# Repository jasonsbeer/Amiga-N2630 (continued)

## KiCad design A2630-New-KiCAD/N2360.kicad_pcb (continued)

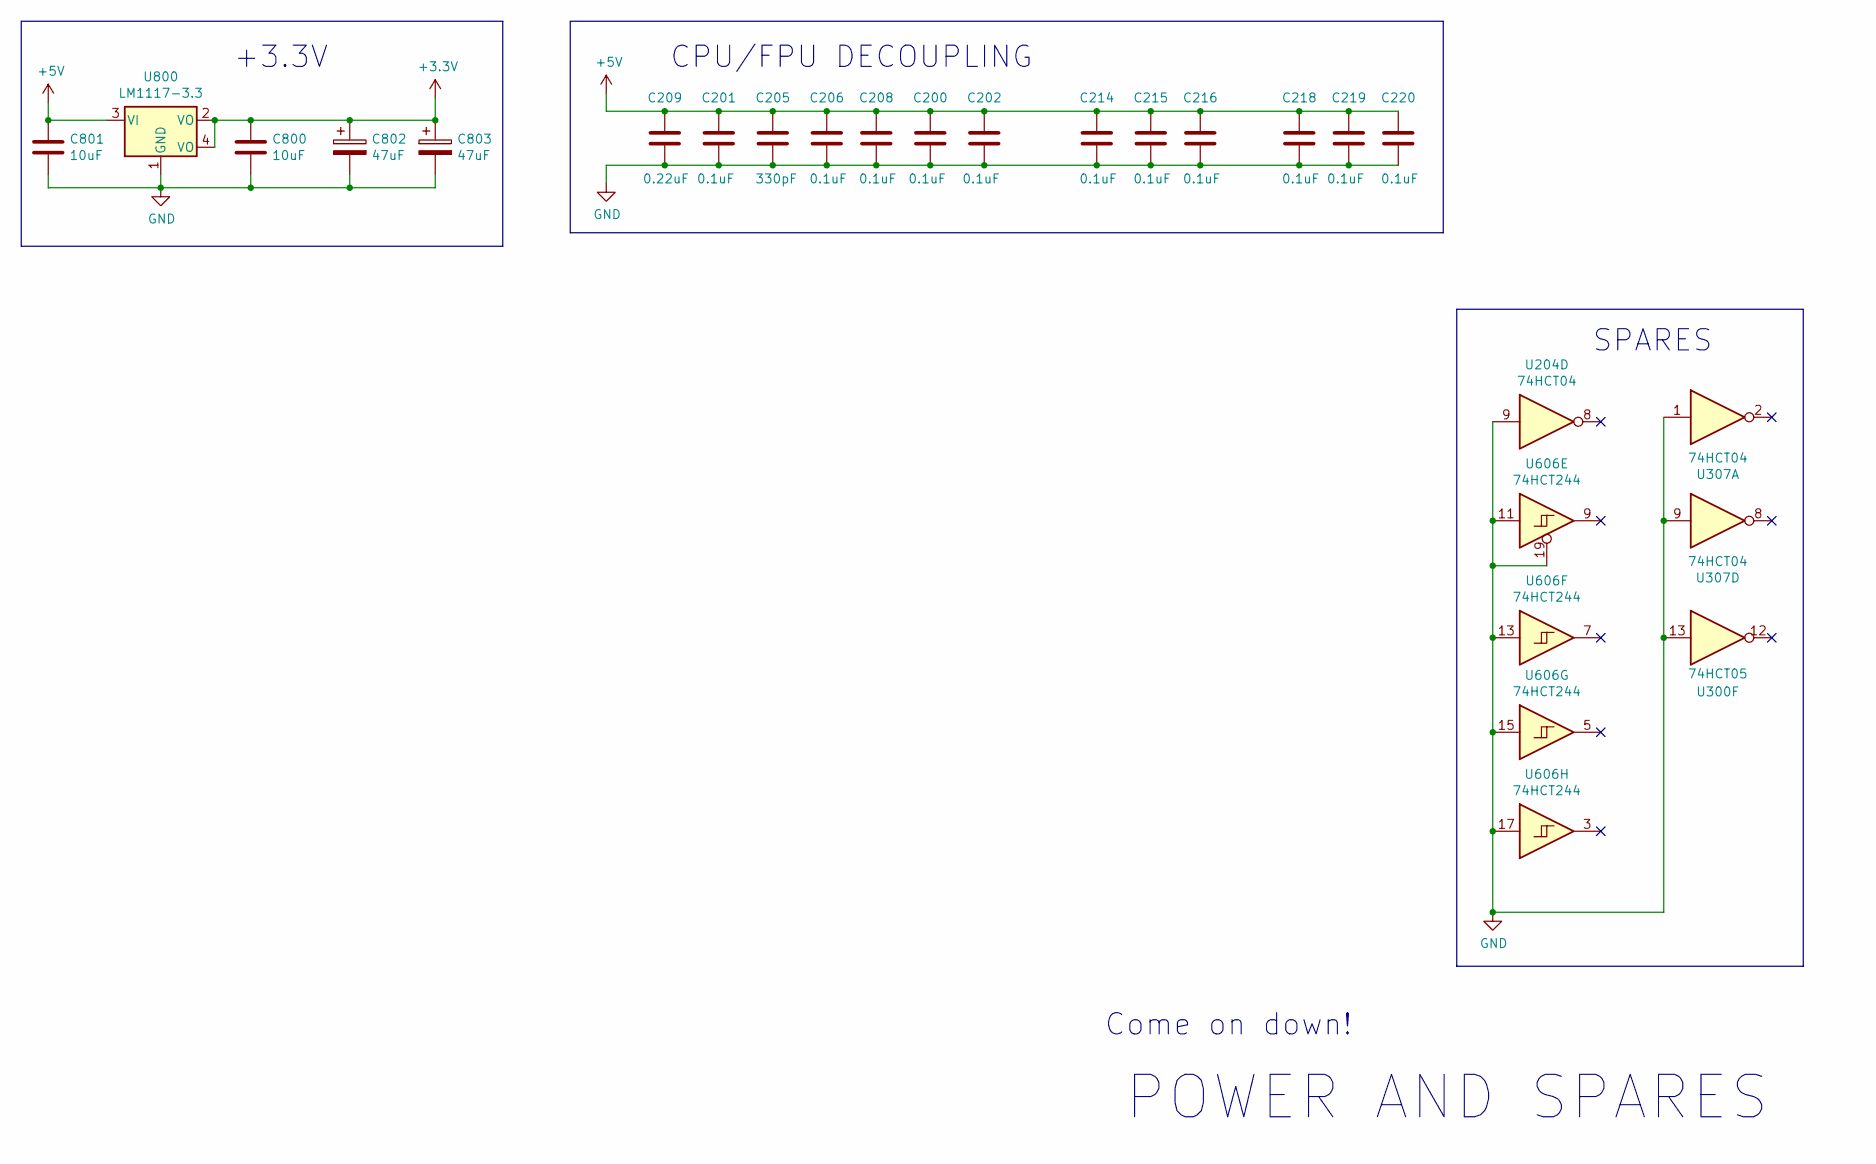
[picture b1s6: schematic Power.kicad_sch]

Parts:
C200, C201, C202, C206, C208, C214, C215, C216, C218, C219, C220: 0.1uF; C_0805_2012Metric
C205: 330pF; C_0805_2012Metric
C209: 0.22uF; C_0805_2012Metric
C800, C801: 10uF; R_0805_2012Metric
C802, C803: 47uF; CP_Radial_D5.0mm_P2.00mm
U204: 74HCT04; SOIC-14_3.9x8.7mm_P1.27mm; Digikey 296-31832-1-ND
U300: 74HCT05; SOIC-14_3.9x8.7mm_P1.27mm
U307: 74HCT04; SOIC-14_3.9x8.7mm_P1.27mm
U606: 74HCT244; SOIC-20W_7.5x12.8mm_P1.27mm
U800: LM1117-3.3; SOT-223

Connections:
+3V3: C800.1, C802.1, C803.1, U800.2 (VO), U800.4 (VO); also elsewhere on the board

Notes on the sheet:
POWER AND SPARES
Come on down!
SPARES
+3.3V
CPU/FPU DECOUPLING

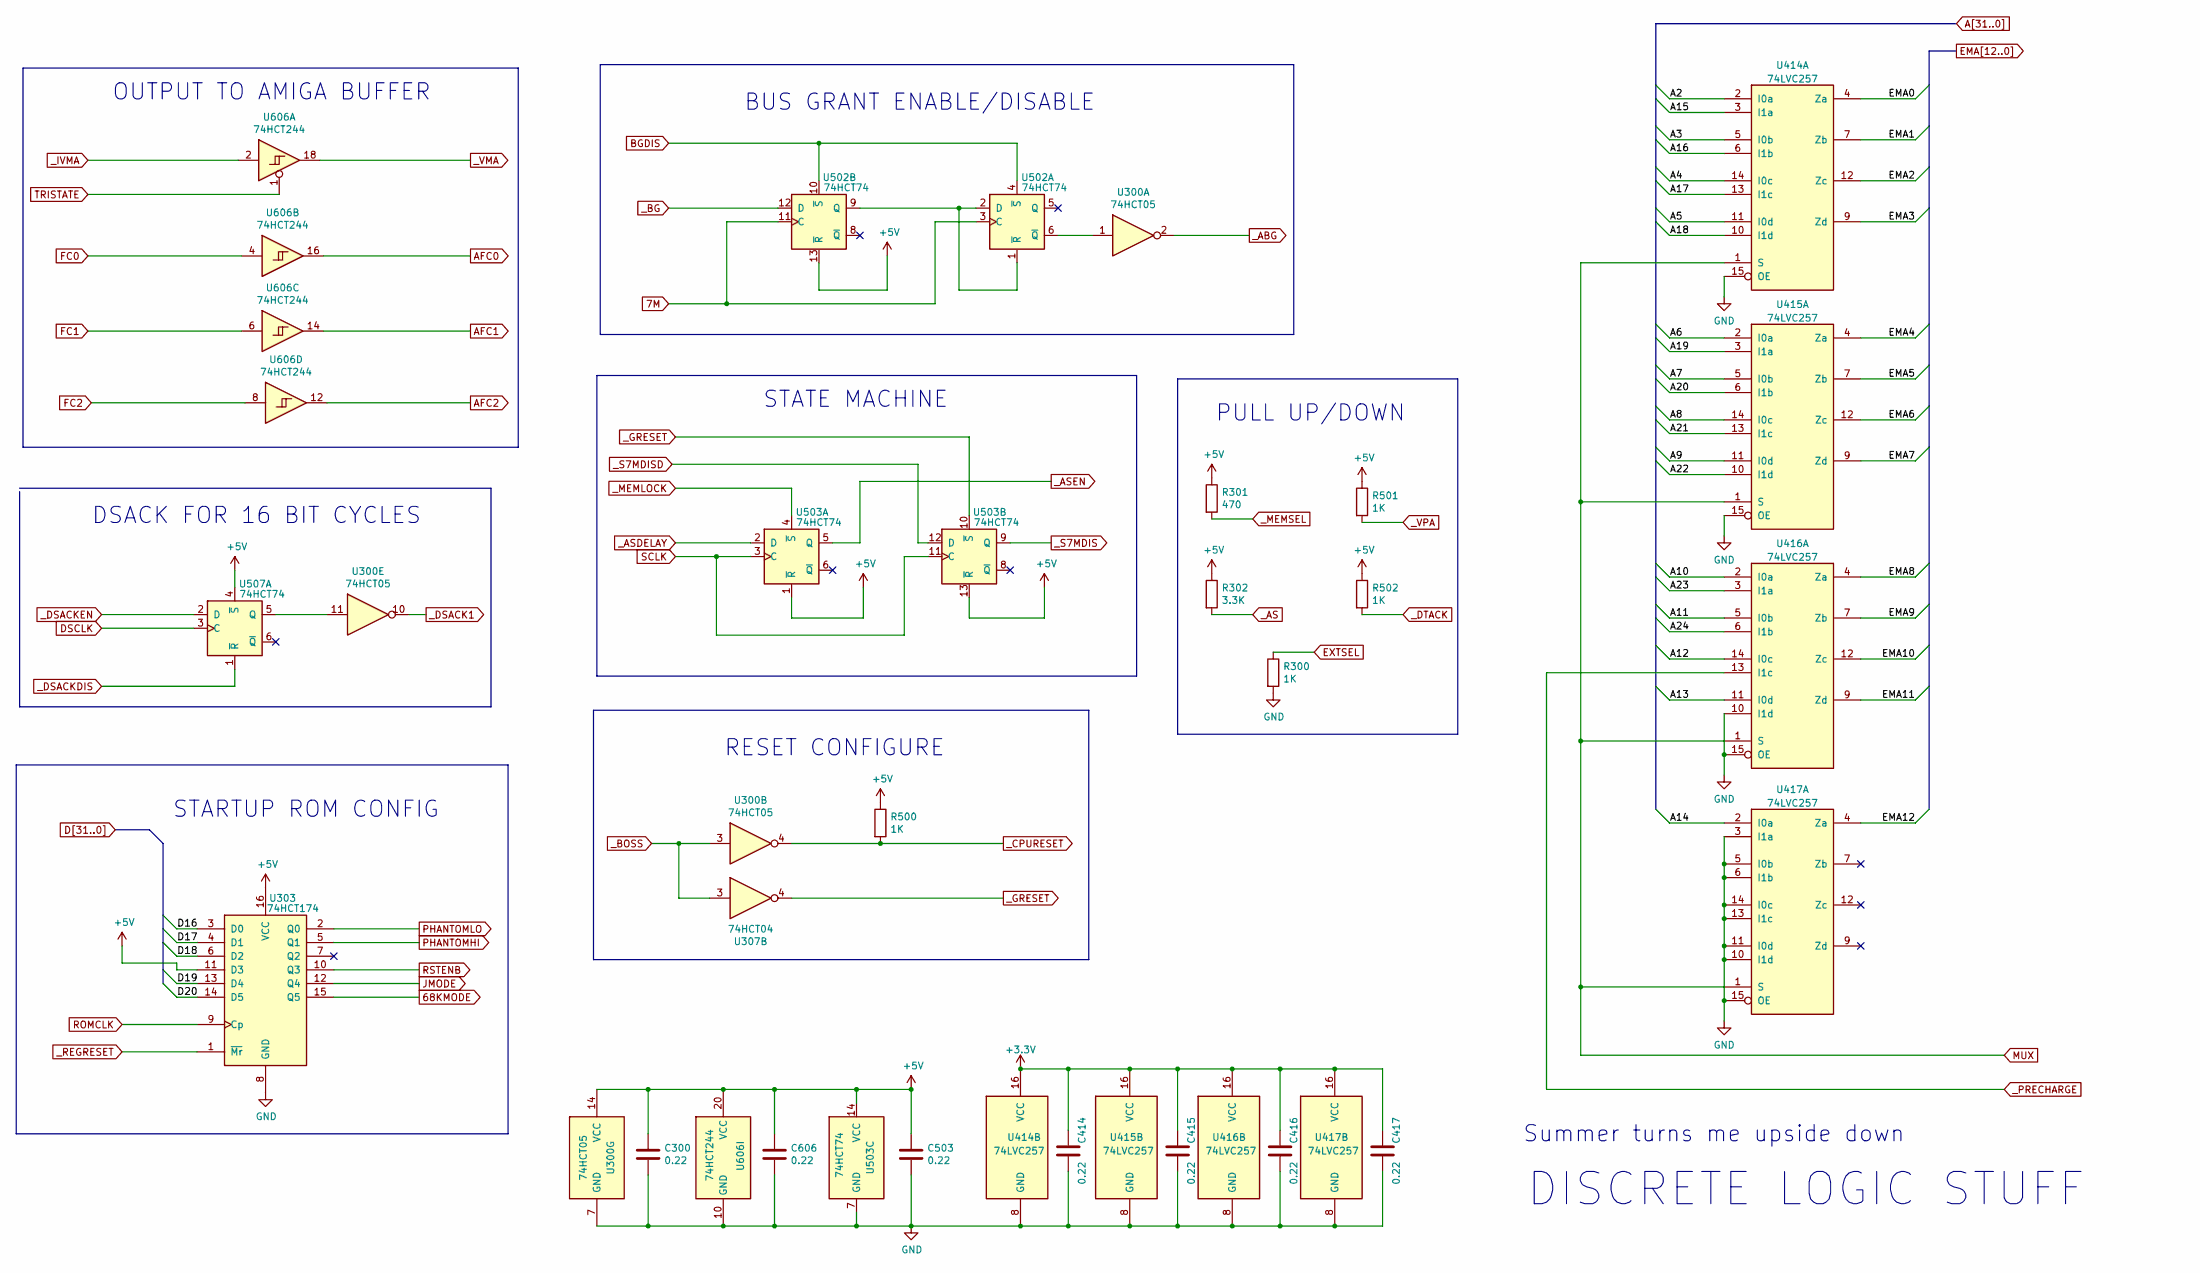
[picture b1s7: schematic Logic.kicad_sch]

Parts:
C300, C414, C415, C416, C417, C503, C606: 0.22; C_0805_2012Metric
R300, R500, R501, R502: 1K; R_0805_2012Metric
R301: 470; R_0805_2012Metric
R302: 3.3K; R_0805_2012Metric
U300: 74HCT05; SOIC-14_3.9x8.7mm_P1.27mm
U303: 74HCT174; SOIC-16_3.9x9.9mm_P1.27mm
U307: 74HCT04; SOIC-14_3.9x8.7mm_P1.27mm
U414, U415, U416, U417: 74LVC257; SOIC-16_3.9x9.9mm_P1.27mm
U502, U503, U507: 74HCT74; SOIC-14_3.9x8.7mm_P1.27mm
U606: 74HCT244; SOIC-20W_7.5x12.8mm_P1.27mm

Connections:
7M: U502.3 (C), U502.11 (C); also elsewhere on the board
68KMODE: U303.15 (Q5)
+3V3: C414.1, C415.1, C416.1, C417.1, U414.16 (VCC), U415.16 (VCC), U416.16 (VCC), U417.16 (VCC); also elsewhere on the board
A2: U414.2 (I0a); also elsewhere on the board
A3: U414.5 (I0b); also elsewhere on the board
A4: U414.14 (I0c); also elsewhere on the board
A5: U414.11 (I0d); also elsewhere on the board
A6: U415.2 (I0a); also elsewhere on the board
A7: U415.5 (I0b); also elsewhere on the board
A8: U415.14 (I0c); also elsewhere on the board
A9: U415.11 (I0d); also elsewhere on the board
A10: U416.2 (I0a); also elsewhere on the board
A11: U416.5 (I0b); also elsewhere on the board
A12: U416.14 (I0c); also elsewhere on the board
A13: U416.11 (I0d); also elsewhere on the board
A14: U417.2 (I0a); also elsewhere on the board
A15: U414.3 (I1a); also elsewhere on the board
A16: U414.6 (I1b); also elsewhere on the board
A17: U414.13 (I1c); also elsewhere on the board
A18: U414.10 (I1d); also elsewhere on the board
A19: U415.3 (I1a); also elsewhere on the board
A20: U415.6 (I1b); also elsewhere on the board
A21: U415.13 (I1c); also elsewhere on the board
A22: U415.10 (I1d); also elsewhere on the board
A23: U416.3 (I1a); also elsewhere on the board
A24: U416.6 (I1b); also elsewhere on the board
AFC0: U606.16; also elsewhere on the board
AFC1: U606.14; also elsewhere on the board
AFC2: U606.12; also elsewhere on the board
BGDIS: U502.4 (~S), U502.10 (~S)
D16: U303.3 (D0); also elsewhere on the board
D17: U303.4 (D1); also elsewhere on the board
D18: U303.6 (D2); also elsewhere on the board
D19: U303.13 (D4); also elsewhere on the board
D20: U303.14 (D5); also elsewhere on the board
DSCLK: U507.3 (C); also elsewhere on the board
EMA0: U414.4 (Za); also elsewhere on the board
EMA1: U414.7 (Zb); also elsewhere on the board
EMA2: U414.12 (Zc); also elsewhere on the board
EMA3: U414.9 (Zd); also elsewhere on the board
EMA4: U415.4 (Za); also elsewhere on the board
EMA5: U415.7 (Zb); also elsewhere on the board
EMA6: U415.12 (Zc); also elsewhere on the board
EMA7: U415.9 (Zd); also elsewhere on the board
EMA8: U416.4 (Za); also elsewhere on the board
EMA9: U416.7 (Zb); also elsewhere on the board
EMA10: U416.12 (Zc); also elsewhere on the board
EMA11: U416.9 (Zd); also elsewhere on the board
EMA12: U417.4 (Za); also elsewhere on the board
EXTSEL: R300.1; also elsewhere on the board
FC0: U606.4; also elsewhere on the board
FC1: U606.6; also elsewhere on the board
FC2: U606.8; also elsewhere on the board
JMODE: U303.12 (Q4); also elsewhere on the board
MUX: U414.1 (S), U415.1 (S), U416.1 (S), U417.1 (S); also elsewhere on the board
unnamed: U300.1, U502.6 (~Q)
unnamed: U300.11, U507.5 (Q)
unnamed: U502.1 (~R), U502.2 (D), U502.9 (Q)
PHANTOMHI: U303.5 (Q1); also elsewhere on the board
PHANTOMLO: U303.2 (Q0); also elsewhere on the board
ROMCLK: U303.9 (Cp); also elsewhere on the board
RSTENB: U303.10 (Q3)
SCLK: U503.3 (C), U503.11 (C); also elsewhere on the board
TRISTATE: U606.1; also elsewhere on the board
_ABG: U300.2; also elsewhere on the board
_AS: R302.2; also elsewhere on the board
_ASDELAY: U503.2 (D); also elsewhere on the board
_ASEN: U503.5 (Q); also elsewhere on the board
_BG: U502.12 (D); also elsewhere on the board
_BOSS: U300.3, U307.3; also elsewhere on the board
_CPURESET: R500.2, U300.4; also elsewhere on the board
_DSACK1: U300.10; also elsewhere on the board
_DSACKDIS: U507.1 (~R); also elsewhere on the board
_DSACKEN: U507.2 (D); also elsewhere on the board
_DTACK: R502.2; also elsewhere on the board
_GRESET: U307.4, U503.10 (~S); also elsewhere on the board
_IVMA: U606.2; also elsewhere on the board
_MEMLOCK: U503.4 (~S); also elsewhere on the board
_MEMSEL: R301.2; also elsewhere on the board
_PRECHARGE: U416.13 (I1c); also elsewhere on the board
_REGRESET: U303.1 (~Mr); also elsewhere on the board
_S7MDIS: U503.9 (Q); also elsewhere on the board
_S7MDISD: U503.12 (D); also elsewhere on the board
_VMA: U606.18; also elsewhere on the board
_VPA: R501.2; also elsewhere on the board

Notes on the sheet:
STARTUP ROM CONFIG
PULL UP/DOWN
RESET CONFIGURE
Summer turns me upside down
DSACK FOR 16 BIT CYCLES
DISCRETE LOGIC STUFF
OUTPUT TO AMIGA BUFFER
BUS GRANT ENABLE/DISABLE
STATE MACHINE

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
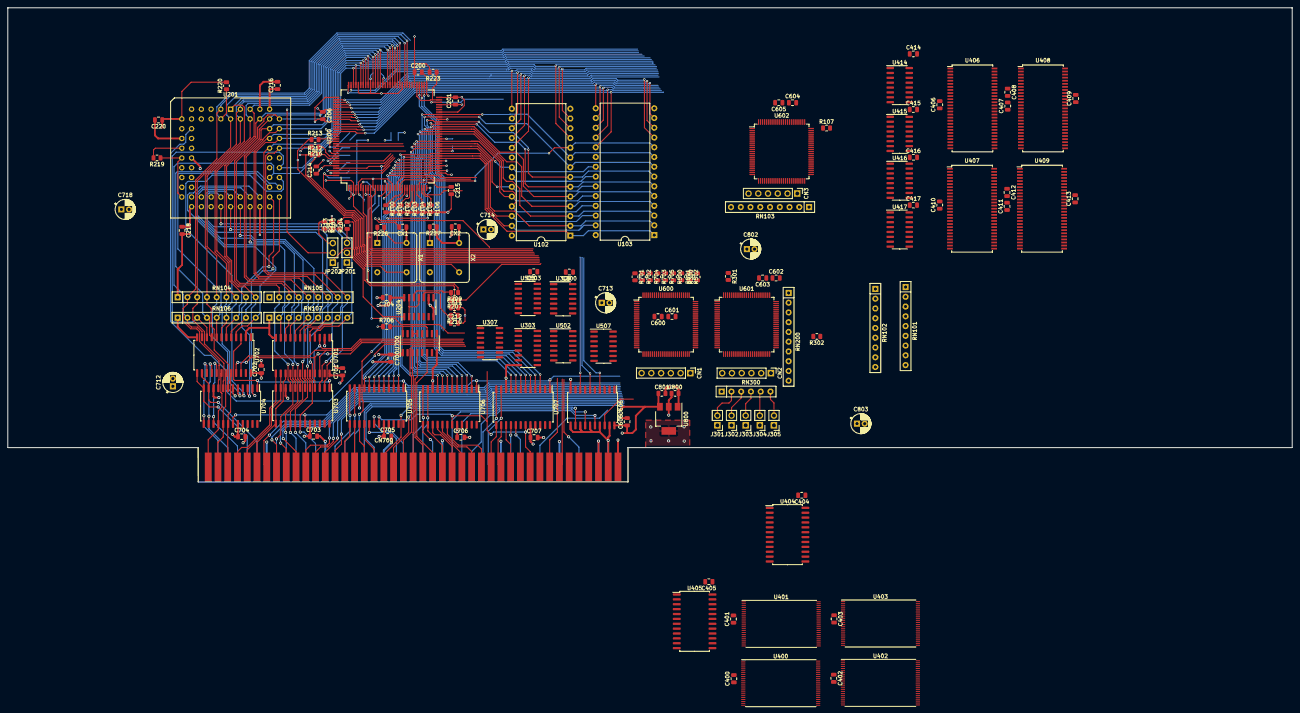
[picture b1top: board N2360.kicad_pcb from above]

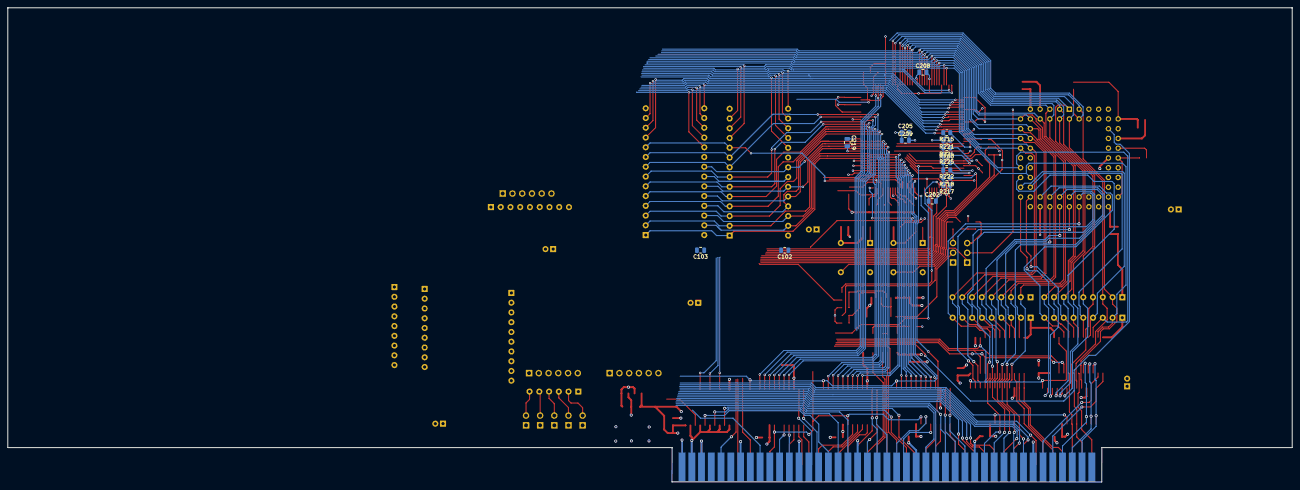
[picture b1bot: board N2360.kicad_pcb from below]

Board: 4 copper layers, 334.4 x 123.5 mm, 166 parts (15 on the bottom side), 297 nets.

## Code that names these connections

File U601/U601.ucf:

NET "nBGACK"		LOC = "P1" ;
NET "EXTSEL"		LOC = "P3" ;
NET "PHANTOMLO"	LOC = "P4" ;
NET "PHANTOMHI"	LOC = "P6" ;
NET "FC<0>"			LOC = "P8" ;
NET "FC<1>"			LOC = "P9" ;
NET "nSENSE"		LOC = "P12" ; 
NET "nBERR"			LOC = "P13" ;
NET "nCPURESET"	LOC = "P14" ;
NET "CPUCLK"		LOC = "P22" ; //15
NET "nMEMLOCK"		LOC = "P16" ;
NET "nASEN"			LOC = "P17" ;
NET "nEXTERN"		LOC = "P18" ;
//NET "nMEMSEL"		LOC = "P20" ;
NET "nONBOARD"		LOC = "P15" ; //22
NET "nDSEN"			LOC = "P23" ;
NET "nCYCEND"		LOC = "P25" ;
NET "CONFIGED"		LOC = "P27" ;
//NET "ARnW"			LOC = "P28" ;
NET "TRISTATE"		LOC = "P29" ;
NET "nUDS"			LOC = "P30" ;
NET "nLDS"			LOC = "P33" ;
NET "MEMACCESS"	LOC = "P39" ; //
NET "nRESET"		LOC = "P37" ; //
//NET "TWOMB"			LOC = "P35" ; //35
NET "Z2AUTO"		LOC = "P36" ; 

//NET "MODE68K"		LOC = "P40" ; //
NET "OSMODE"		LOC = "P42" ; //
//NET "nOE0"			LOC = "P49" ; //
NET "nLMBE"			LOC = "P50" ; //
NET "nLLBE"			LOC = "P52" ; //
NET "nUUBE"			LOC = "P53" ; //
NET "nUMBE"			LOC = "P54" ; //
//NET "nWE0"			LOC = "P55" ; //
NET "SIZ<0>"		LOC = "P56" ; //
NET "SIZ<1>"		LOC = "P58" ; //
//NET "EMDDIR"		LOC = "P59" ; //

NET "A<0>"			LOC = "P60" ; //60
NET "A<1>"			LOC = "P61" ; //61
NET "A<2>"			LOC = "P63" ; //
NET "A<3>"			LOC = "P64" ; //
NET "A<4>"			LOC = "P65" ; //
NET "A<5>"			LOC = "P66" ; //
NET "A<6>"			LOC = "P67" ; //
NET "A<13>"			LOC = "P68" ; //
NET "A<14>"			LOC = "P70" ; //
NET "A<15>"			LOC = "P71" ; //
NET "A<16>"			LOC = "P72" ; //
NET "A<17>"			LOC = "P74" ; //
NET "A<18>"			LOC = "P76" ; //
NET "A<19>"			LOC = "P77" ; //
NET "A<20>"			LOC = "P78" ; //
NET "A<21>"			LOC = "P79" ; //
NET "A<22>"			LOC = "P81" ; //81
NET "A<23>"			LOC = "P82" ; //82

NET "D<28>"			LOC = "P86" ; //86
NET "D<29>"			LOC = "P85" ; 
NET "D<30>"			LOC = "P91" ; //90
NET "D<31>"			LOC = "P89" ; 

NET "nCIIN"			LOC = "P87" ;
NET "FC<2>"			LOC = "P90" ; //91
NET "nAVEC"			LOC = "P92" ;
NET "nDS"			LOC = "P93" ;
NET "nAS"			LOC = "P94" ;
NET "RnW"			LOC = "P95" ;
NET "nFPUCS"		LOC = "P96" ;
NET "nCSROM"		LOC = "P97" ;
NET "ROMCLK"		LOC = "P99" ;

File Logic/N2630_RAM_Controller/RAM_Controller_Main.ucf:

NET	"A<0>"	LOC = "P82"	;
NET	"A<1>"	LOC = "P81"	;
NET	"A<2>"	LOC = "P79"	;
NET	"A<3>"	LOC = "P78"	;
NET	"A<4>"	LOC = "P77"	;
NET	"A<5>"	LOC = "P76"	;
NET	"A<6>"	LOC = "P74"	;
NET	"A<7>"	LOC = "P72"	;
NET	"A<8>"	LOC = "P71"	;
NET	"A<9>"	LOC = "P70"	;
NET	"A<10>"	LOC = "P68"	;
NET	"A<11>"	LOC = "P67"	;
NET	"A<12>"	LOC = "P66"	;
NET	"A<13>"	LOC = "P65"	;
NET	"A<14>"	LOC = "P64"	;
NET	"A<15>"	LOC = "P63"	;
NET	"A<16>"	LOC = "P61"	;
NET	"A<17>"	LOC = "P60"	;
NET	"A<18>"	LOC = "P59"	;
NET	"A<19>"	LOC = "P58"	;
NET	"A<20>"	LOC = "P56"	;
NET	"A<21>"	LOC = "P55"	;
NET	"A<22>"	LOC = "P54"	;
NET	"A<23>"	LOC = "P53"	;
NET	"A<24>"	LOC = "P52"	;
NET	"A<25>"	LOC = "P50"	;
NET	"A<26>"	LOC = "P49"	;
NET	"A<27>"	LOC = "P42"	;
NET	"A<28>"	LOC = "P41"	;
NET	"A<29>"	LOC = "P37"	;
NET	"A<30>"	LOC = "P35"	;
NET	"A<31>"	LOC = "P32"	;

NET	"MA<0>"	LOC = "P13"	;
NET	"MA<1>"	LOC = "P14"	;
NET	"MA<2>"	LOC = "P15"	;
NET	"MA<3>"	LOC = "P16"	;
NET	"MA<4>"	LOC = "P17"	;
NET	"MA<5>"	LOC = "P18"	;
NET	"MA<6>"	LOC = "P20"	;
NET	"MA<7>"	LOC = "P23"	;
NET	"MA<8>"	LOC = "P25"	;
NET	"MA<9>"	LOC = "P27"	;
NET	"MA<10>"	LOC = "P28"	;
NET	"MA<11>"	LOC = "P29"	;
NET	"MA<12>"	LOC = "P30"	;

NET	"D<0>"	LOC = "P3";
NET	"D<1>"	LOC = "P4";
NET	"D<2>"	LOC = "P6";
NET	"D<3>"	LOC = "P8";

NET	"_RAS"	LOC = "P33"	;
NET	"_CAS"	LOC = "P36"	;

NET	"_CBREQ"	LOC = "P87"	;
NET	"_AS"		LOC = "P91"	;
NET	"_DS"		LOC = "P90"	;
NET	"SIZ0"	LOC = "P92"	;
NET	"SIZ1"	LOC = "P93"	;
NET	"_STERM"	LOC = "P94"	;
NET	"_CBACK"	LOC = "P95"	;
NET	"_DSACK0"	LOC = "P96"	;
NET	"_DSACK1"	LOC = "P97"	;

NET	"CPUCLK_A"	LOC = "P22"	;
NET	"_GRESET"	LOC = "P99" ;

NET	"DQM0"	LOC = "P9"	;
NET	"DQM1"	LOC = "P10"	;
NET	"DQM2"	LOC = "P11"	;
NET	"DQM3"	LOC = "P12"	;

NET	"BANK0"	LOC = "P39"	;
NET	"BANK1"	LOC = "P40"	;

NET 	"FC0"		LOC = "P85"	;
NET 	"FC1"		LOC = "P86"	;
NET 	"FC2"		LOC = "P89"	;

#Address Timings
#From the 68030 user manual...
#The processor places the address on the bus at the beginning of 
#a bus cycle. The address is valid while AS is asserted.
#AS is a timing signal that indicates the validity of an address on the address
#bus and of many control signals. It is asserted one-half clock after the 
#beginning of a bus cycle.
INST	"A<0>"	TNM = ADDRESS	;
INST	"A<1>"	TNM = ADDRESS	;
INST	"A<2>"	TNM = ADDRESS	;
INST	"A<3>"	TNM = ADDRESS	;
INST	"A<4>"	TNM = ADDRESS	;
INST	"A<5>"	TNM = ADDRESS	;
INST	"A<6>"	TNM = ADDRESS	;
INST	"A<7>"	TNM = ADDRESS	;
INST	"A<8>"	TNM = ADDRESS	;
INST	"A<9>"	TNM = ADDRESS	;
INST	"A<10>"	TNM = ADDRESS	;
INST	"A<11>"	TNM = ADDRESS	;
INST	"A<12>"	TNM = ADDRESS	;
INST	"A<13>"	TNM = ADDRESS	;
INST	"A<14>"	TNM = ADDRESS	;
INST	"A<15>"	TNM = ADDRESS	;
INST	"A<16>"	TNM = ADDRESS	;
INST	"A<17>"	TNM = ADDRESS	;
INST	"A<18>"	TNM = ADDRESS	;
INST	"A<19>"	TNM = ADDRESS	;
INST	"A<20>"	TNM = ADDRESS	;
INST	"A<21>"	TNM = ADDRESS	;
INST	"A<22>"	TNM = ADDRESS	;
INST	"A<23>"	TNM = ADDRESS	;
INST	"A<24>"	TNM = ADDRESS	;
INST	"A<25>"	TNM = ADDRESS	;
INST	"A<26>"	TNM = ADDRESS	;
INST	"A<27>"	TNM = ADDRESS	;
INST	"A<28>"	TNM = ADDRESS	;
INST	"A<29>"	TNM = ADDRESS	;
INST	"A<30>"	TNM = ADDRESS	;
INST	"A<31>"	TNM = ADDRESS	;
TIMEGRP "ADDRESS" OFFSET - IN 1 ns VALID 100 ns BEFORE "_AS" FALLING;

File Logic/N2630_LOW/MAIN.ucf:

NET "nS7MDISD"	LOC = "P1" ;
NET "SCLK"		LOC = "P3" ;
NET "nS7MDIS"	LOC = "P4" ;
NET "nBOSS"		LOC = "P6" ;
NET "nASDELAY"	LOC = "P8" ;
NET "nDSACKDIS"	LOC = "P9" ;
NET "IPLCLK"	LOC = "P10" ;
NET "nDSACKEN"	LOC = "P11" ;	
NET "nDSCLK"	LOC = "P12" ;

NET "ADDIR"		LOC = "P13" ;
NET "DRSEL"		LOC = "P14"	;
NET "nADOEH"	LOC = "P15" ;
NET "P7M"		LOC = "P16" ;
NET "nC1"		LOC = "P17" ;
NET "nC3"		LOC = "P18" ;
NET "nADOEL"	LOC = "P20" ;
NET "nAAS"		LOC = "P22" ;
NET "nUDS"		LOC = "P23" ;
NET "nLDS"		LOC = "P25" ;
NET "nDTACK"	LOC = "P28" ;
NET "nABG"		LOC = "P29" ;
NET "nABGACK"	LOC = "P30" ;
NET "nABR"		LOC = "P33" ;
NET "nRESET"	LOC = "P35" ;
NET "E"			LOC = "P36" ;
NET "nVPA"		LOC = "P37" ;
NET "nOVR"		LOC = "P39" ;
NET "nBGACK"	LOC = "P40" ;
NET "nIVMA"		LOC = "P41" ;
NET "B2000"		LOC = "P42" ;
NET "TRISTATE"	LOC = "P49" ;	
NET "CONFIGED"	LOC = "P50" ;
NET "ARnW"		LOC = "P52" ;
NET "CDAC"		LOC = "P53" ;
NET "A7M"		LOC = "P54" ;
NET "MEMACCESS"	LOC = "P55" ;	
NET "nBGDIS"		LOC = "P58" ;
NET "nCYCEND"	LOC = "P60" ;
NET "DSEN"		LOC = "P61" ;
NET "nONBOARD"	LOC = "P63" ;
NET "nMEMSEL"	LOC = "P64" ;

NET "nEXTERN"	LOC = "P65" ;
NET "nASEN"		LOC = "P66" ;
NET "CPUCLK"	LOC = "P67" ;
NET "nCPURESET"	LOC = "P68" ;
NET "EXTSEL"	LOC = "P70" ;
NET "FC<2>"		LOC = "P71" ;
NET "FC<1>"		LOC = "P72" ;
NET "FC<0>"		LOC = "P74" ;
NET "n7M"		LOC = "P76" ;
NET "nAS"		LOC = "P85" ;
NET "RnW"		LOC = "P86" ;
NET "nSTERM"	LOC = "P87" ;
NET "nHALT"		LOC = "P90" ;
NET "nDSACK1"	LOC = "P92" ;
NET "nDSACK0"	LOC = "P93" ;
NET "RSTENB"	LOC = "P94" ;
NET "JMODE"		LOC = "P95" ;
NET "MODE68K"	LOC = "P96" ;
NET "nREGRESET"	LOC = "P97" ;

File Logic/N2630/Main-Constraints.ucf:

NET	"A<16>"	LOC = "P"	;
NET	"A<17>"	LOC = "P"	;
NET	"A<18>"	LOC = "P"	;
NET	"A<19>"	LOC = "P"	;
NET	"A<20>"	LOC = "P"	;
NET	"A<21>"	LOC = "P"	;
NET	"A<22>"	LOC = "P"	;
NET	"A<23>"	LOC = "P"	;

NET "PHANTOMHI"	LOC = "P" ;
NET "PHANTOMLO"	LOC = "P" ;

NET "_AS"	LOC = "P" ;
NET "R_W"	LOC = "P" ;
NET "_BOSS"	LOC = "P" ;
NET "_ABG"	LOC = "P" ;
NET "_AAS" 	LOC = "P" ;

NET "FC0"	LOC = "P" ;
NET "FC1"	LOC = "P" ;
NET "FC2"	LOC = "P" ;

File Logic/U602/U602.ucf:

NET "A<0>" 		LOC="P41";
NET "A<1>" 		LOC="P43";
NET "A<2>" 		LOC="P44";
NET "A<3>" 		LOC="P45";
NET "A<4>" 		LOC="P46";
NET "A<5>" 		LOC="P48";
NET "A<6>" 		LOC="P49";
NET "A<7>" 		LOC="P50";
NET "A<8>" 		LOC="P51";
NET "A<9>" 		LOC="P52";
NET "A<10>" 	LOC="P53";
NET "A<11>" 	LOC="P54";
NET "A<12>" 	LOC="P56";
NET "A<13>" 	LOC="P57";
NET "A<14>" 	LOC="P58";
NET "A<15>" 	LOC="P59";
NET "A<16>" 	LOC="P60";
NET "A<17>" 	LOC="P61";
NET "A<18>" 	LOC="P64";
NET "A<19>" 	LOC="P66";
NET "A<20>" 	LOC="P68";
NET "A<21>" 	LOC="P69";
NET "A<22>" 	LOC="P70";
NET "A<23>" 	LOC="P71";
NET "A<24>" 	LOC="P40";
NET "A<25>" 	LOC="P39";
NET "A<26>" 	LOC="P35";
NET "A<27>" 	LOC="P34";
NET "A<28>" 	LOC="P33";
NET "A<29>" 	LOC="P31";
NET "A<30>" 	LOC="P38";
NET "A<31>" 	LOC="P27";

NET "D<24>"		LOC="P4";
NET "D<25>"		LOC="P143";
NET "D<26>"		LOC="P142";
NET "D<27>"		LOC="P22";
NET "D<28>"		LOC="P23";
NET "D<29>"		LOC="P24";
NET "D<30>"		LOC="P25";
NET "D<31>"		LOC="P26";

//NET "nBERR"		LOC="P5";
//NET "nCBREQ"	LOC="P7";
//NET "nCBACK"	LOC="P9";
NET "EXTSEL"	LOC="P10";
NET "nBGACK"	LOC="P11";
NET "nSTERM"	LOC="P12";
NET "FC<0>"		LOC="P13";
NET "FC<1>"		LOC="P14";
NET "FC<2>"		LOC="P15";
//NET "nDSACK0"	LOC="P16";
NET "nDSACK1"	LOC="P17";
NET "nDS"		LOC="P19";
NET "nAS"		LOC="P20";
NET "RnW"		LOC="P21";
NET "CPUCLK"	LOC="P30";
NET "nEM1LLBE"	LOC="P74";
NET "nEM1UMBE"	LOC="P75";
NET "nEM1LMBE"	LOC="P76";
NET "nEM1UUBE"	LOC="P77";
NET "nEM1WE"	LOC="P78";
NET "nCAS1"		LOC="P79";
NET "EM1CLKE"	LOC="P80";
NET "nRAS1"		LOC="P81";
NET "EMA<7>"	LOC="P82";
NET "nEM1CS"	LOC="P83";
NET "EMA<5>"	LOC="P85";
NET "BANK0"		LOC="P86";
NET "EMA<6>"	LOC="P87";
NET "BANK1"		LOC="P88";
NET "EMA<4>"	LOC="P91";
NET "EMA<3>"	LOC="P92";
NET "EMA<1>"	LOC="P93";
NET "EMA<2>"	LOC="P94";
NET "EMA<0>"	LOC="P95";
NET "EMA<12>"	LOC="P96";
NET "EMA<11>"	LOC="P97";
NET "EMA<9>"	LOC="P98";
NET "EMA<10>"	LOC="P100";
NET "EMA<8>"	LOC="P101";
NET "nEM0LLBE"	LOC="P102";
NET "nEM0UUBE"	LOC="P103";
NET "nEM0LMBE"	LOC="P104";
NET "nEM0UMBE"	LOC="P105";
NET "nCAS0"		LOC="P107";
NET "nEM0WE"		LOC="P106";
NET "EM0CLKE"	LOC="P110";
NET "nRAS0"		LOC="P111";
NET "nEM0CS"	LOC="P112";
//NET "DMARQ"		LOC="P113";
NET "nDIOW"		LOC="P115";
NET "nDIOR"		LOC="P116";
NET "IORDY"		LOC="P117";
//NET "nDMACK"	LOC="P118";
NET "INTRQ"		LOC="P119";
//NET "nIO16"		LOC="P120";
NET "DA<1>"		LOC="P121";
NET "DA<0>"		LOC="P124";
NET "DA<2>"		LOC="P125";
NET "nCS0"		LOC="P126";
NET "nCS1"		LOC="P128";
NET "MODE68K"	LOC="P131";
NET "nDTACK"	LOC="P132";
NET "nIDEDIS"	LOC="P133";
NET "nRESET"	LOC="P134";
//NET "nINT2"		LOC="P135";
//NET "nOVR"		LOC="P136";
NET "nGRESET"	LOC="P137";
NET "SIZ<1>"		LOC="P138";
NET "SIZ<0>"		LOC="P139";
NET "nZ3DIS"	LOC="P140";

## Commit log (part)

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2022-11-12 More Robust PIO Mode Support
2022-11-12 Simplified SDRAM Address Logic
2022-11-12 Updated Z3 Ram Section
2022-11-13 Lock out ATA during Z3 access.
2022-11-17 50MHz ROM Fix
2022-11-18 50MHz DSACK Fix
2022-11-20 50MHz DSACK Overhaul
    Redid all the DSACK logic to better support 50MHz timings.
2022-11-26 Replaced by Rev 3.0
2022-12-13 SDRAM Fix for 50MHz
2022-12-15 Create Rev-30
    CPLD logic for hardware revision 3.0.
2022-12-17 Lockout IDE during CPU cycle.
2022-12-18 74FCT646 Fix
    68000 state machine was not releasing the data bus during CPU cycles.
2022-12-18 74FCT646 fix.
2022-12-18 Zorro 2 50MHz SDRAM fix.
2022-12-20 AUTOCONFIG delay fix.
2022-12-20 AUTOCONFIG DSACKx delay fix.
2023-01-05 Z3 AUTOCONFIG Disable
2023-01-10 Fixes flaky 68000 R_W signal.
2023-01-13 Relaxed Z2 SDRAM Read Timing
2023-01-14 Zorro 3 Timing Fix
2023-01-22 Add PCB info.
2023-01-22 Fixed issues link.
2023-01-23 Interactive BOM
2023-01-23 Removed unused components.
2023-01-23 Exclude non-BOM items.
2023-01-24 Fixed 74AHCT04 part number.
2023-02-03 Fixed bus grant.
2023-02-05 Add copper pours to top and bottom layers.
2023-02-14 DMA Fix
2023-02-15 Photos
2023-02-15 Spelling
2023-02-16 Fixed CPU Menu
2023-02-18 Rev 4.0.0 68882 PLCC
2023-02-18 Rev 4.0.0 MC68882-PGA
2023-02-19 Added EPROM speed.
2023-02-20 Added A2000 bracket.
2023-02-20 A2000 bracket.
2023-02-20 Update KiCAD Files
2023-02-20 Rev 4.0.0 Schematics
2023-02-26 Added ROM delay.
2023-02-26 Fixed Zorro 3 cycle DSACK contention.
2023-03-04 U600 X
2023-03-21 Exp U600 Logic
2023-04-03 Add EATX Bracket
2023-09-05 U600 Logic for HW Rev 4
2023-09-11 Rev 4 Logic
2023-09-17 SM Logic 17-SEPT-23
2023-09-24 Update TestedDevices.md
    Added X-Surf 100
2023-10-01 U600 Logic v2.0.3
2023-10-01 Remove v2.0.0 VHDL code.
2023-10-01 Added U600 v2.0.3 JED file.
2023-10-04 Add Rev 4.0.1 Hardware
2023-10-05 U600 Rev 2.0.4 Logic
2023-10-10 Added U600 Rev 2.0.4 Firmware
2023-10-11 New INT Logic U602
2023-10-12 Updated U602 Firmware
2023-10-12 U600 Firmware Rev 2.0.5
2023-10-13 U600 Rev 2.0.6
2023-10-15 Updated U600 Rev 2.0.6
2023-10-15 U600 Updates
2023-10-15 Add U600 Rev 2.0.7 Firmware
2023-10-19 U600 Firmware 2.0.7-SE
2023-10-25 U600 Rev 2.0.8 Fixed instability with rev 4.x B2000
2023-10-25 U600 v2.0.8
2023-10-26 U600 Rev 2.0.8 Final Fixed DSACK Process
2023-10-26 File clean up.
2023-10-26 6800/68000 State Machine Output U600 Rev 2.0.8 Firmware
2023-10-27 U602 1.1.1 Fixed Gayle ID register after soft reset
2023-10-28 RESET Glitch Fix
    Changes from LIV2
2023-10-28 Removed _CPURESET from U600 Constraints.
2023-10-28 Add Newest JED Files
2023-10-28 Update U600 Macrocell power level.
2023-10-29 U600 Rev 2.0.10 WordSync Fix
2023-11-04 U601 Rev 1.2.4
    Fixes DSACK glitch when ROMs selected.
2023-11-05 Cleanup Files
2023-11-05 Logic Updates
2023-11-05 Push Rev 4.0.1 KiCAD and Gerber.
2023-11-05 Push Rev 4.0.1a/b schematics.
2023-11-05 Push Rev 4.0.1a/b IBOM
2023-11-05 Fix IBOM File Name
2023-11-05 Add JLCPCB images.
2023-11-06 JLCPCB Image
2023-12-08 Speed Enhanced Logic 07-DEC-2023
2023-12-08 XGecu Images
2023-12-11 U601 Rev 2.0.1
2023-12-27 Fix missing component values on gerber silkscreen. 26-DEC-2023
2024-03-27 Revision 4.1.0
2024-03-27 Rename KiCAD Folders
2024-03-27 Add Rev 4.0.1x to Archive
